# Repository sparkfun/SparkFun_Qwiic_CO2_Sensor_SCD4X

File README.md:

SparkFun CO₂ Humidity and Temperature Sensor - SCD4x (Qwiic)
========================================

<table class="table table-hover table-striped table-bordered">
    <tr>
        <th class="text-center">
        </th>
        <th class="text-center">
        </th>
    </tr>
    <tr align="center">
        <td></td>
        <td></td>
    </tr>
    <tr align="center">
        <td><a href="https://www.sparkfun.com/products/22395">SparkFun CO₂ Humidity and Temperature Sensor - SCD40 (Qwiic)</a></td>
        <td><a href="https://www.sparkfun.com/products/22396">SparkFun CO₂ Humidity and Temperature Sensor - SCD41 (Qwiic)</a></td>
    </tr>
</table>

The SparkFun CO<sub>2</sub> Humidity and Temperature Sensor - SCD4x (Qwiic) features the SCD40 and SCD41 CO<sub>2</sub> sensors from Sensirion<sup>&copy;</sup>. The SCD4x sensors use Sensirion's PASens<sup>&reg;</sup> photoacoustic measurement system that combines narrow-band IR light and a microphone inside the sensing package capable of detecting concentrations from 0 to 40000 ppm with high accuracy. The SCD40 has best accuracy over 400-2000 ppm ±(50 ppm+5%) and the SCD41 has best accuracy over 400-5000 ppm ±(40 ppm+5%). The SCD4x have an integrated temperature and humidity CMos<sup>&reg;</sup> sensor to improve accuracy. For additional accuracy the SCD4x also accept ambient pressure readings!

Repository Contents
-------------------

* **/Documentation** - Data sheets, additional product information
* **/Hardware** - Eagle design files (.brd, .sch)
* **/Production** - Production panel files (.brd)
* **/docs** - Online documentation files

Documentation
--------------
* **[SparkFun SCD4x CO<sub>2</sub> Sensor Arduino Library](https://github.com/sparkfun/SparkFun_SCD4x_Arduino_Library)** - Arduino library for the SparkFun CO₂ Humidity and Temperature Sensor - SCD4x (Qwiic).
* **[Hookup Guide](https://sparkfun.github.io/SparkFun_Qwiic_CO2_Sensor_SCD4X)** - Basic hookup guide for the SparkFun Qwiic CO<sub>2</sub> Sensor - SCD4x.
* **[SparkFun Fritzing repo](https://github.com/sparkfun/Fritzing_Parts)** - Fritzing diagrams for SparkFun products.

Product Versions
----------------
* [SEN-22935](https://www.sparkfun.com/products/22395) - Qwiic CO<sub>2</sub> Sensor - SCD40
* [SEN-22396](https://www.sparkfun.com/products/22395) - Qwiic CO<sub>2</sub> Sensor - SCD41

Version History
---------------
* [SCD40 v10](https://www.sparkfun.com/products/22395) - Initial SparkFun release (SCD40)
* [SCD41 v10](https://www.sparkfun.com/products/22396) - Initial SparkFun release (SCD41)
* [SparkX SCD40 v01](https://www.sparkfun.com/products/18365) - Initial SparkX release (SCD40)
* [SparkX SCD41 v01](https://www.sparkfun.com/products/18366) - Initial SparkX release (SCD41)

License Information
-------------------

This product is _**open source**_!

Please review the LICENSE.md file for license information.

If you have any questions or concerns on licensing, please contact technical support on our [SparkFun forums](https://forum.sparkfun.com/viewforum.php?f=152).

Distributed as-is; no warranty is given.

- Your friends at SparkFun.

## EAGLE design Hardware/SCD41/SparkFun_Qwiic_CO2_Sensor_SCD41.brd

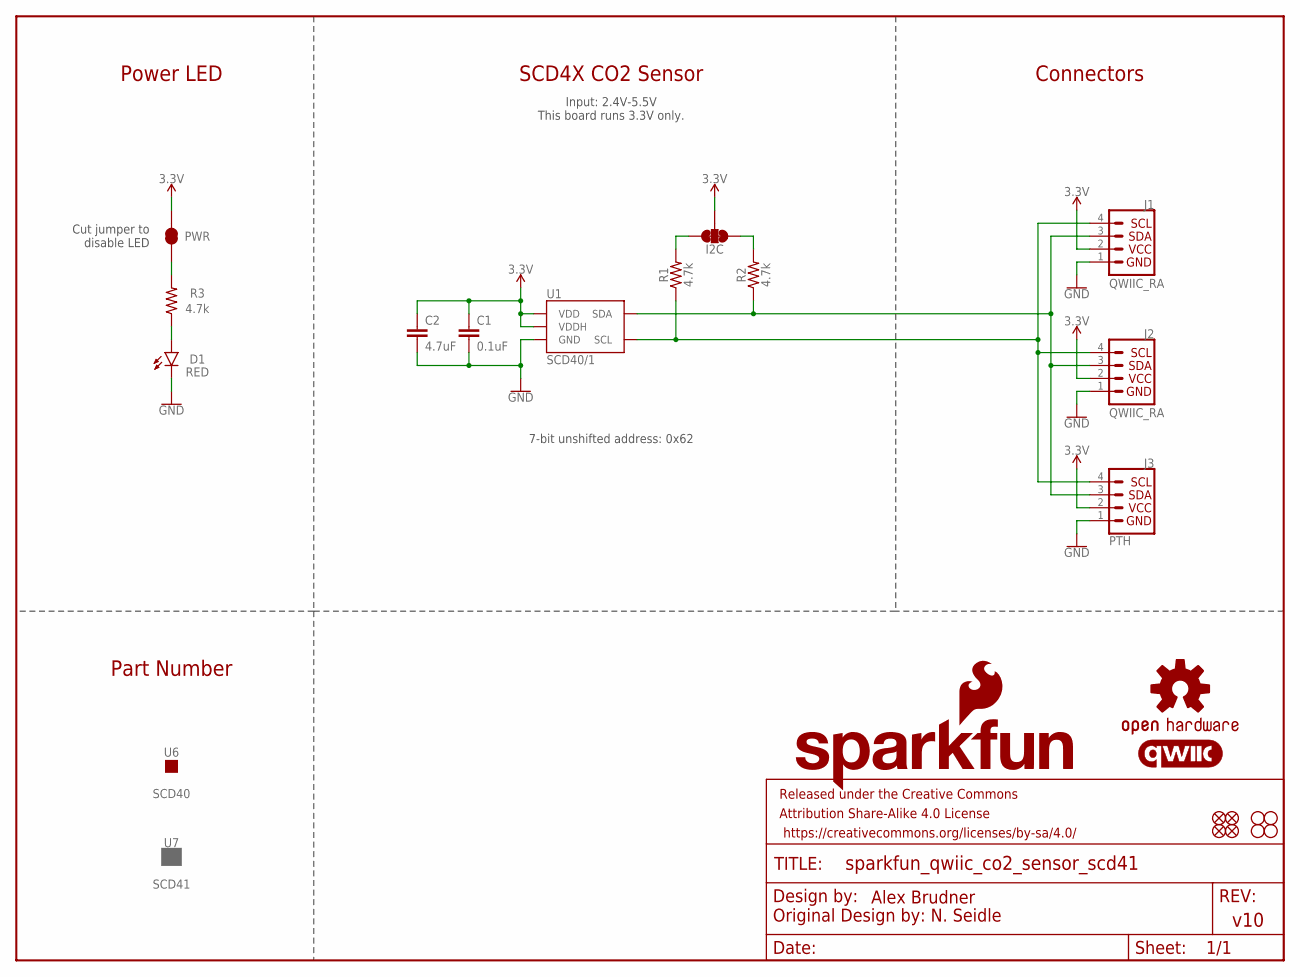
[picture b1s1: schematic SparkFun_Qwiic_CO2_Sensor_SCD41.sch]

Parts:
C1: 0.1uF; 0603
C2: 4.7uF; 0603
D1: RED; LED-0603
FD1, FD2, FD3, FD4: FIDUCIALUFIDUCIAL; FIDUCIAL-MICRO
FRAME1: FRAME-LETTER; CREATIVE_COMMONS
H1, H2, H3, H4: STAND-OFF
I2C: I2C; SMT-JUMPER_3_2-NC_TRACE_SILK
J1, J2: QWIIC_RA; JST04_1MM_RA
J3: PTH; 1X04_NO_SILK
LOGO1: QWIIC_LOGO_CONNECTOR; QWIIC_5.5MM
LOGO2: OSHW-LOGOS; OSHW-LOGO-S
LOGO3: SFE_LOGO_NAME_FLAMEBLANK; BLANK
PWR: PWR; SMT-JUMPER_2_NC_TRACE_SILK
R1, R2, R3: 4.7k; 0603
U1: SCD40/1; SCD4X
U6: SCD40; PRODUCT_IDENT_NO_NO-SILK
U7: SCD41; PRODUCT_IDENT_PASTE_NO-SILK

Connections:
3.3V: C1.1, C2.1, I2C.2, J1.2, J2.2, J3.2, PWR.2, U1.7 (VDD), U1.19 (VDDH)
GND: C1.2, C2.2, D1.C, J1.1, J2.1, J3.1, U1.6 (GND), U1.20 (GND), U1.CP (GND)
unnamed: I2C.1, R2.2
unnamed: I2C.3, R1.2
unnamed: PWR.1, R3.2
unnamed: D1.A, R3.1
SCL: J1.4, J2.4, J3.4, R1.1, U1.9 (SCL)
SDA: J1.3, J2.3, J3.3, R2.1, U1.10 (SDA)

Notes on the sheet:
Cut jumper to disable LED
SCD4X CO2 Sensor
Power LED
Connectors
Part Number
Input: 2.4V-5.5V This board runs 3.3V only.
7-bit unshifted address: 0x62

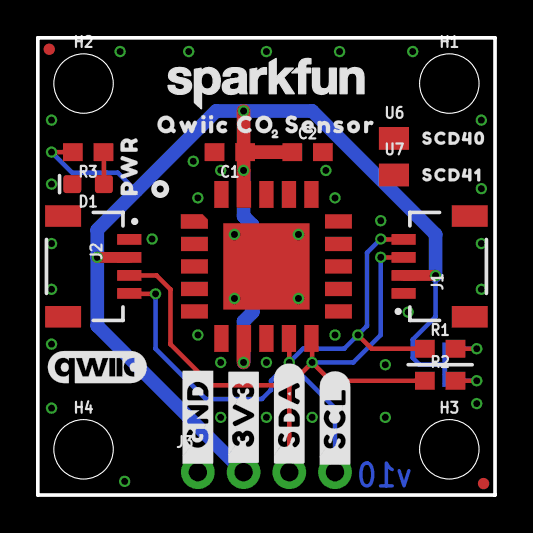
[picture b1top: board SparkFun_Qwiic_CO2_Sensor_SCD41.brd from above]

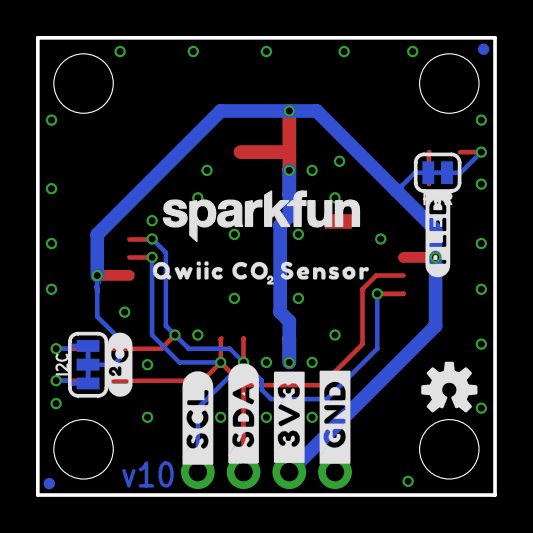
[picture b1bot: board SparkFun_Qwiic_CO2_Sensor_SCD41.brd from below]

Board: 2 copper layers, 25.4 x 25.4 mm, 49 parts (16 on the bottom side), 8 nets.

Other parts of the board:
U$1, U$18: #_GND#14
U$2, U$19: #_3V3#15
U$3, U$20: #_SDA#15
U$4, U$21: #_SCL#16
U$5, U$12: SFE_LOGO_NAME_.1
U$6: SCD414140404021
U$7: SCD40414140404022
U$8, U$13: QWIIC_CO0
U$9, U$14: SENSOR0
U$10, U$15: 20
U$11: SFE_LOGO_FLAME_STOP_.1
U$16: #PLED#21
U$17: #I�C#0
U$22: ORDERING_INSTRUCTIONS
U$23: PWR0

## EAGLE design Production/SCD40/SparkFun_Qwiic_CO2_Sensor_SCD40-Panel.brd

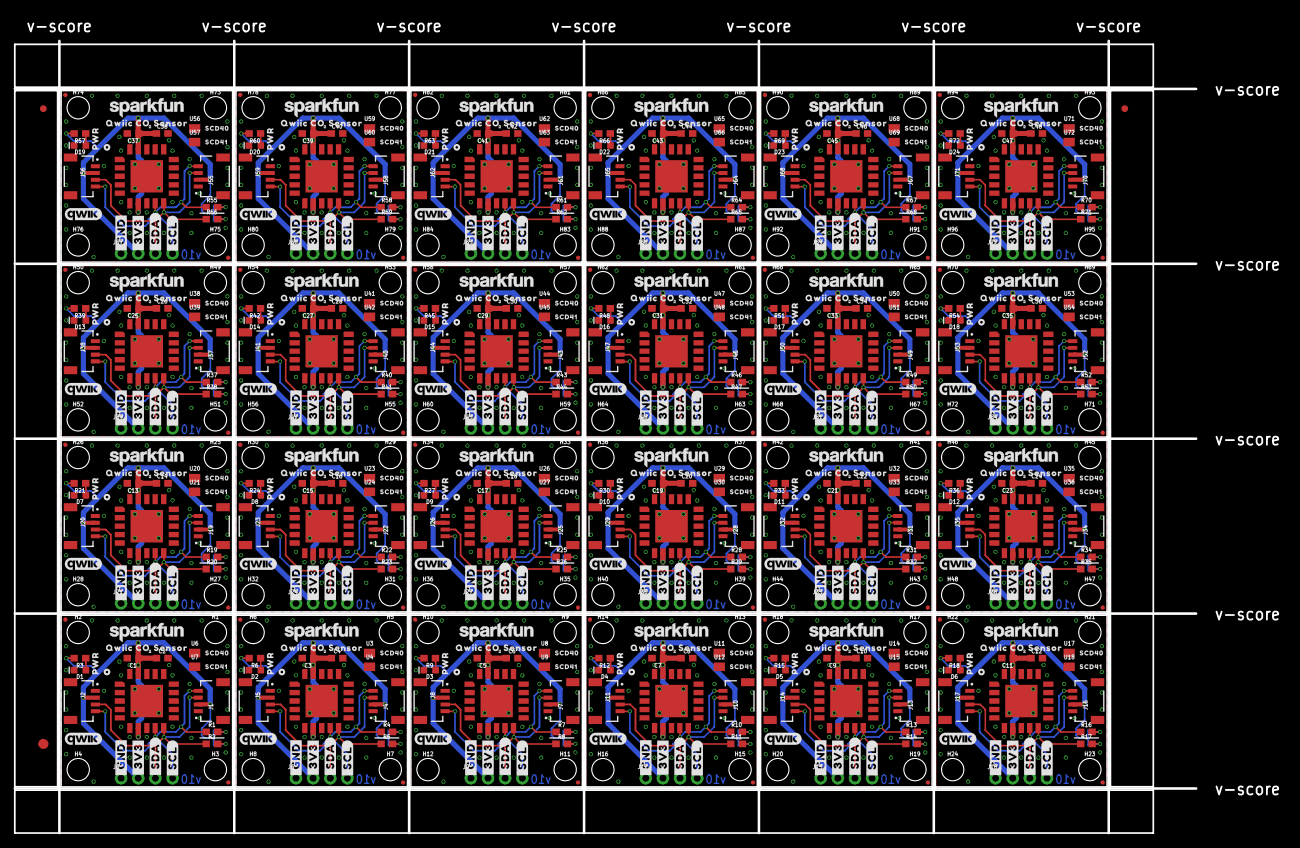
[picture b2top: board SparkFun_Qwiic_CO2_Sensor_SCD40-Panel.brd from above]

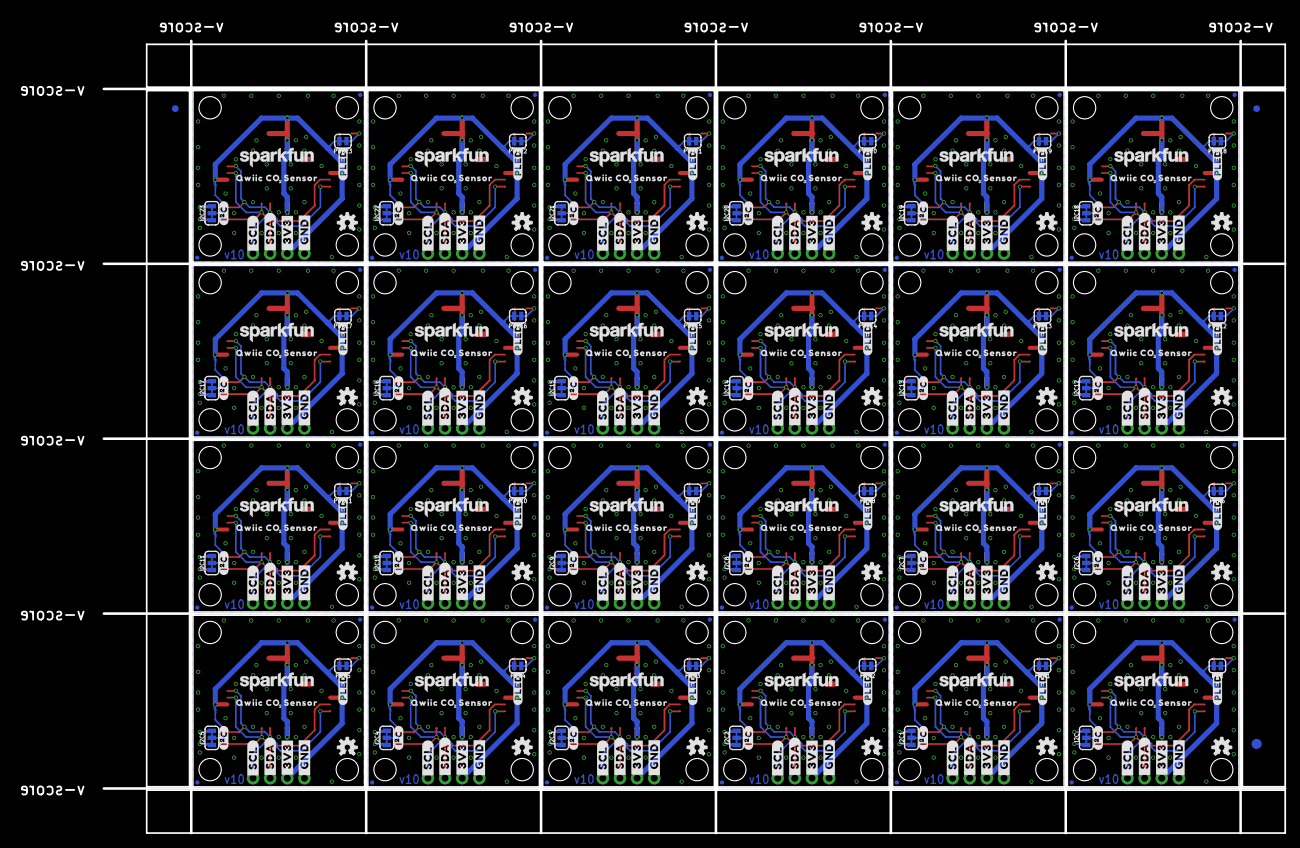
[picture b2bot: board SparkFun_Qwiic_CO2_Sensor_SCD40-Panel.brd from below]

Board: 2 copper layers, 175.0 x 117.3 mm, 1134 parts (387 on the bottom side), 192 nets.

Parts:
C1, C3, C5, C7, C9, C11, C13, C15, C17, C19, C21, C23, C25, C27, C29, C31, C33, C35, C37, C39, C41, C43, C45, C47: 0.1uF; 0603
C2, C4, C6, C8, C10, C12, C14, C16, C18, C20, C22, C24, C26, C28, C30, C32, C34, C36, C38, C40, C42, C44, C46, C48: 4.7uF; 0603
D1, D2, D3, D4, D5, D6, D7, D8, D9, D10, D11, D12, D13, D14, D15, D16, D17, D18, D19, D20, D21, D22, D23, D24: RED; LED-0603
E$1, E$2, E$3, E$4: FIDUCIAL-1X2
E$5, E$6: FIDUCIAL-1.5X3
FD1, FD2, FD3, FD4, FD5, FD6, FD7, FD8, FD9, FD10, FD11, FD12, FD13, FD14, FD15, FD16, FD17, FD18, FD19, FD20, FD21, FD22, FD23, FD24, FD25, FD26, FD27, FD28, FD29, FD30, FD31, FD32, FD33, FD34, FD35, FD36, FD37, FD38, FD39, FD40, FD41, FD42, FD43, FD44, FD45, FD46, FD47, FD48, FD49, FD50, FD51, FD52, FD53, FD54, FD55, FD56, FD57, FD58, FD59, FD60, FD61, FD62, FD63, FD64, FD65, FD66, FD67, FD68, FD69, FD70, FD71, FD72, FD73, FD74, FD75, FD76, FD77, FD78, FD79, FD80, FD81, FD82, FD83, FD84, FD85, FD86, FD87, FD88, FD89, FD90, FD91, FD92, FD93, FD94, FD95, FD96: FIDUCIALUFIDUCIAL; FIDUCIAL-MICRO
H1, H2, H3, H4, H5, H6, H7, H8, H9, H10, H11, H12, H13, H14, H15, H16, H17, H18, H19, H20, H21, H22, H23, H24, H25, H26, H27, H28, H29, H30, H31, H32, H33, H34, H35, H36, H37, H38, H39, H40, H41, H42, H43, H44, H45, H46, H47, H48, H49, H50, H51, H52, H53, H54, H55, H56, H57, H58, H59, H60, H61, H62, H63, H64, H65, H66, H67, H68, H69, H70, H71, H72, H73, H74, H75, H76, H77, H78, H79, H80, H81, H82, H83, H84, H85, H86, H87, H88, H89, H90, H91, H92, H93, H94, H95, H96: STAND-OFF
I2C, I2C1, I2C2, I2C3, I2C4, I2C5, I2C6, I2C7, I2C8, I2C9, I2C10, I2C11, I2C12, I2C13, I2C14, I2C15, I2C16, I2C17, I2C18, I2C19, I2C20, I2C21, I2C22, I2C23: I2C; SMT-JUMPER_3_2-NC_TRACE_SILK
J1, J2, J4, J5, J7, J8, J10, J11, J13, J14, J16, J17, J19, J20, J22, J23, J25, J26, J28, J29, J31, J32, J34, J35, J37, J38, J40, J41, J43, J44, J46, J47, J49, J50, J52, J53, J55, J56, J58, J59, J61, J62, J64, J65, J67, J68, J70, J71: QWIIC_RA; JST04_1MM_RA
J3, J6, J9, J12, J15, J18, J21, J24, J27, J30, J33, J36, J39, J42, J45, J48, J51, J54, J57, J60, J63, J66, J69, J72: PTH; 1X04_NO_SILK
LOGO1, LOGO4, LOGO7, LOGO10, LOGO13, LOGO16, LOGO19, LOGO22, LOGO25, LOGO28, LOGO31, LOGO34, LOGO37, LOGO40, LOGO43, LOGO46, LOGO49, LOGO52, LOGO55, LOGO58, LOGO61, LOGO64, LOGO67, LOGO70: QWIIC_LOGO_CONNECTOR; QWIIC_5.5MM
LOGO2, LOGO5, LOGO8, LOGO11, LOGO14, LOGO17, LOGO20, LOGO23, LOGO26, LOGO29, LOGO32, LOGO35, LOGO38, LOGO41, LOGO44, LOGO47, LOGO50, LOGO53, LOGO56, LOGO59, LOGO62, LOGO65, LOGO68, LOGO71: OSHW-LOGOS; OSHW-LOGO-S
LOGO3, LOGO6, LOGO9, LOGO12, LOGO15, LOGO18, LOGO21, LOGO24, LOGO27, LOGO30, LOGO33, LOGO36, LOGO39, LOGO42, LOGO45, LOGO48, LOGO51, LOGO54, LOGO57, LOGO60, LOGO63, LOGO66, LOGO69, LOGO72: SFE_LOGO_NAME_FLAMEBLANK; BLANK
PWR, PWR1, PWR2, PWR3, PWR4, PWR5, PWR6, PWR7, PWR8, PWR9, PWR10, PWR11, PWR12, PWR13, PWR14, PWR15, PWR16, PWR17, PWR18, PWR19, PWR20, PWR21, PWR22, PWR23: PWR; SMT-JUMPER_2_NC_TRACE_SILK
R1, R2, R4, R5, R7, R8, R10, R11, R13, R14, R16, R17, R19, R20, R22, R23, R25, R26, R28, R29, R31, R32, R34, R35, R37, R38, R40, R41, R43, R44, R46, R47, R49, R50, R52, R53, R55, R56, R58, R59, R61, R62, R64, R65, R67, R68, R70, R71: 2.2k; 0603
R3, R6, R9, R12, R15, R18, R21, R24, R27, R30, R33, R36, R39, R42, R45, R48, R51, R54, R57, R60, R63, R66, R69, R72: 4.7k; 0603
U1, U2, U5, U10, U13, U16, U19, U22, U25, U28, U31, U34, U37, U40, U43, U46, U49, U52, U55, U58, U61, U64, U67, U70: SCD40/1; SCD4X
U3, U6, U8, U11, U14, U17, U20, U23, U26, U29, U32, U35, U38, U41, U44, U47, U50, U53, U56, U59, U62, U65, U68, U71: SCD40; PRODUCT_IDENT_PASTE_NO-SILK
U4, U7, U9, U12, U15, U18, U21, U24, U27, U30, U33, U36, U39, U42, U45, U48, U51, U54, U57, U60, U63, U66, U69, U72: SCD41; PRODUCT_IDENT_NO_NO-SILK
U$1, U$18, U$22, U$39, U$45, U$61, U$67, U$83, U$89, U$105, U$111, U$127, U$133, U$149, U$155, U$171, U$177, U$193, U$199, U$215, U$221, U$237, U$243, U$259, U$265, U$281, U$287, U$303, U$309, U$325, U$331, U$347, U$353, U$369, U$375, U$391, U$397, U$413, U$419, U$435, U$441, U$457, U$463, U$479, U$485, U$501, U$507, U$523: #_GND#14
U$2, U$19, U$24, U$40, U$46, U$62, U$68, U$84, U$90, U$106, U$112, U$128, U$134, U$150, U$156, U$172, U$178, U$194, U$200, U$216, U$222, U$238, U$244, U$260, U$266, U$282, U$288, U$304, U$310, U$326, U$332, U$348, U$354, U$370, U$376, U$392, U$398, U$414, U$420, U$436, U$442, U$458, U$464, U$480, U$486, U$502, U$508, U$524: #_3V3#15
U$3, U$20, U$25, U$41, U$47, U$63, U$69, U$85, U$91, U$107, U$113, U$129, U$135, U$151, U$157, U$173, U$179, U$195, U$201, U$217, U$223, U$239, U$245, U$261, U$267, U$283, U$289, U$305, U$311, U$327, U$333, U$349, U$355, U$371, U$377, U$393, U$399, U$415, U$421, U$437, U$443, U$459, U$465, U$481, U$487, U$503, U$509, U$525: #_SDA#15
U$4, U$21, U$26, U$42, U$48, U$64, U$70, U$86, U$92, U$108, U$114, U$130, U$136, U$152, U$158, U$174, U$180, U$196, U$202, U$218, U$224, U$240, U$246, U$262, U$268, U$284, U$290, U$306, U$312, U$328, U$334, U$350, U$356, U$372, U$378, U$394, U$400, U$416, U$422, U$438, U$444, U$460, U$466, U$482, U$488, U$504, U$510, U$526: #_SCL#16
U$5, U$12, U$27, U$34, U$49, U$56, U$71, U$78, U$93, U$100, U$115, U$122, U$137, U$144, U$159, U$166, U$181, U$188, U$203, U$210, U$225, U$232, U$247, U$254, U$269, U$276, U$291, U$298, U$313, U$320, U$335, U$342, U$357, U$364, U$379, U$386, U$401, U$408, U$423, U$430, U$445, U$452, U$467, U$474, U$489, U$496, U$511, U$518: SFE_LOGO_NAME_.1
U$6, U$28, U$50, U$72, U$94, U$116, U$138, U$160, U$182, U$204, U$226, U$248, U$270, U$292, U$314, U$336, U$358, U$380, U$402, U$424, U$446, U$468, U$490, U$512: SCD414140404021
U$7, U$29, U$51, U$73, U$95, U$117, U$139, U$161, U$183, U$205, U$227, U$249, U$271, U$293, U$315, U$337, U$359, U$381, U$403, U$425, U$447, U$469, U$491, U$513: SCD40414140404022
U$8, U$13, U$30, U$35, U$52, U$57, U$74, U$79, U$96, U$101, U$118, U$123, U$140, U$145, U$162, U$167, U$184, U$189, U$206, U$211, U$228, U$233, U$250, U$255, U$272, U$277, U$294, U$299, U$316, U$321, U$338, U$343, U$360, U$365, U$382, U$387, U$404, U$409, U$426, U$431, U$448, U$453, U$470, U$475, U$492, U$497, U$514, U$519: QWIIC_CO0
U$9, U$14, U$31, U$36, U$53, U$58, U$75, U$80, U$97, U$102, U$119, U$124, U$141, U$146, U$163, U$168, U$185, U$190, U$207, U$212, U$229, U$234, U$251, U$256, U$273, U$278, U$295, U$300, U$317, U$322, U$339, U$344, U$361, U$366, U$383, U$388, U$405, U$410, U$427, U$432, U$449, U$454, U$471, U$476, U$493, U$498, U$515, U$520: SENSOR0
U$10, U$15, U$32, U$37, U$54, U$59, U$76, U$81, U$98, U$103, U$120, U$125, U$142, U$147, U$164, U$169, U$186, U$191, U$208, U$213, U$230, U$235, U$252, U$257, U$274, U$279, U$296, U$301, U$318, U$323, U$340, U$345, U$362, U$367, U$384, U$389, U$406, U$411, U$428, U$433, U$450, U$455, U$472, U$477, U$494, U$499, U$516, U$521: 20
U$11, U$33, U$55, U$77, U$99, U$121, U$143, U$165, U$187, U$209, U$231, U$253, U$275, U$297, U$319, U$341, U$363, U$385, U$407, U$429, U$451, U$473, U$495, U$517: SFE_LOGO_FLAME_STOP_.1
U$16, U$38, U$60, U$82, U$104, U$126, U$148, U$170, U$192, U$214, U$236, U$258, U$280, U$302, U$324, U$346, U$368, U$390, U$412, U$434, U$456, U$478, U$500, U$522: #PLED#21
U$17, U$43, U$65, U$87, U$109, U$131, U$153, U$175, U$197, U$219, U$241, U$263, U$285, U$307, U$329, U$351, U$373, U$395, U$417, U$439, U$461, U$483, U$505, U$527: #I�C#0
U$23, U$44, U$66, U$88, U$110, U$132, U$154, U$176, U$198, U$220, U$242, U$264, U$286, U$308, U$330, U$352, U$374, U$396, U$418, U$440, U$462, U$484, U$506, U$528: PWR0

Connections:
3.3V: C1.1, C2.1, I2C.2, J1.2, J2.2, J3.2, PWR.2, U1.7, U1.19
3.3V1: C3.1, C4.1, I2C1.2, J4.2, J5.2, J6.2, PWR1.2, U2.7, U2.19
3.3V2: C5.1, C6.1, I2C2.2, J7.2, J8.2, J9.2, PWR2.2, U5.7, U5.19
3.3V3: C7.1, C8.1, I2C3.2, J10.2, J11.2, J12.2, PWR3.2, U10.7, U10.19
3.3V4: C9.1, C10.1, I2C4.2, J13.2, J14.2, J15.2, PWR4.2, U13.7, U13.19
3.3V5: C11.1, C12.1, I2C5.2, J16.2, J17.2, J18.2, PWR5.2, U16.7, U16.19
3.3V6: C13.1, C14.1, I2C6.2, J19.2, J20.2, J21.2, PWR6.2, U19.7, U19.19
3.3V7: C15.1, C16.1, I2C7.2, J22.2, J23.2, J24.2, PWR7.2, U22.7, U22.19
3.3V8: C17.1, C18.1, I2C8.2, J25.2, J26.2, J27.2, PWR8.2, U25.7, U25.19
3.3V9: C19.1, C20.1, I2C9.2, J28.2, J29.2, J30.2, PWR9.2, U28.7, U28.19
3.3V10: C21.1, C22.1, I2C10.2, J31.2, J32.2, J33.2, PWR10.2, U31.7, U31.19
3.3V11: C23.1, C24.1, I2C11.2, J34.2, J35.2, J36.2, PWR11.2, U34.7, U34.19
3.3V12: C25.1, C26.1, I2C12.2, J37.2, J38.2, J39.2, PWR12.2, U37.7, U37.19
3.3V13: C27.1, C28.1, I2C13.2, J40.2, J41.2, J42.2, PWR13.2, U40.7, U40.19
3.3V14: C29.1, C30.1, I2C14.2, J43.2, J44.2, J45.2, PWR14.2, U43.7, U43.19
3.3V15: C31.1, C32.1, I2C15.2, J46.2, J47.2, J48.2, PWR15.2, U46.7, U46.19
3.3V16: C33.1, C34.1, I2C16.2, J49.2, J50.2, J51.2, PWR16.2, U49.7, U49.19
3.3V17: C35.1, C36.1, I2C17.2, J52.2, J53.2, J54.2, PWR17.2, U52.7, U52.19
3.3V18: C37.1, C38.1, I2C18.2, J55.2, J56.2, J57.2, PWR18.2, U55.7, U55.19
3.3V19: C39.1, C40.1, I2C19.2, J58.2, J59.2, J60.2, PWR19.2, U58.7, U58.19
3.3V20: C41.1, C42.1, I2C20.2, J61.2, J62.2, J63.2, PWR20.2, U61.7, U61.19
3.3V21: C43.1, C44.1, I2C21.2, J64.2, J65.2, J66.2, PWR21.2, U64.7, U64.19
3.3V22: C45.1, C46.1, I2C22.2, J67.2, J68.2, J69.2, PWR22.2, U67.7, U67.19
3.3V23: C47.1, C48.1, I2C23.2, J70.2, J71.2, J72.2, PWR23.2, U70.7, U70.19
GND: C1.2, C2.2, D1.C, J1.1, J2.1, J3.1, U1.6, U1.20, U1.CP
GND1: C3.2, C4.2, D2.C, J4.1, J5.1, J6.1, U2.6, U2.20, U2.CP
GND2: C5.2, C6.2, D3.C, J7.1, J8.1, J9.1, U5.6, U5.20, U5.CP
GND3: C7.2, C8.2, D4.C, J10.1, J11.1, J12.1, U10.6, U10.20, U10.CP
GND4: C9.2, C10.2, D5.C, J13.1, J14.1, J15.1, U13.6, U13.20, U13.CP
GND5: C11.2, C12.2, D6.C, J16.1, J17.1, J18.1, U16.6, U16.20, U16.CP
GND6: C13.2, C14.2, D7.C, J19.1, J20.1, J21.1, U19.6, U19.20, U19.CP
GND7: C15.2, C16.2, D8.C, J22.1, J23.1, J24.1, U22.6, U22.20, U22.CP
GND8: C17.2, C18.2, D9.C, J25.1, J26.1, J27.1, U25.6, U25.20, U25.CP
GND9: C19.2, C20.2, D10.C, J28.1, J29.1, J30.1, U28.6, U28.20, U28.CP
GND10: C21.2, C22.2, D11.C, J31.1, J32.1, J33.1, U31.6, U31.20, U31.CP
GND11: C23.2, C24.2, D12.C, J34.1, J35.1, J36.1, U34.6, U34.20, U34.CP
GND12: C25.2, C26.2, D13.C, J37.1, J38.1, J39.1, U37.6, U37.20, U37.CP
GND13: C27.2, C28.2, D14.C, J40.1, J41.1, J42.1, U40.6, U40.20, U40.CP
GND14: C29.2, C30.2, D15.C, J43.1, J44.1, J45.1, U43.6, U43.20, U43.CP
GND15: C31.2, C32.2, D16.C, J46.1, J47.1, J48.1, U46.6, U46.20, U46.CP
GND16: C33.2, C34.2, D17.C, J49.1, J50.1, J51.1, U49.6, U49.20, U49.CP
GND17: C35.2, C36.2, D18.C, J52.1, J53.1, J54.1, U52.6, U52.20, U52.CP
GND18: C37.2, C38.2, D19.C, J55.1, J56.1, J57.1, U55.6, U55.20, U55.CP
GND19: C39.2, C40.2, D20.C, J58.1, J59.1, J60.1, U58.6, U58.20, U58.CP
GND20: C41.2, C42.2, D21.C, J61.1, J62.1, J63.1, U61.6, U61.20, U61.CP
GND21: C43.2, C44.2, D22.C, J64.1, J65.1, J66.1, U64.6, U64.20, U64.CP
GND22: C45.2, C46.2, D23.C, J67.1, J68.1, J69.1, U67.6, U67.20, U67.CP
GND23: C47.2, C48.2, D24.C, J70.1, J71.1, J72.1, U70.6, U70.20, U70.CP
unnamed: I2C1.1, R5.2
unnamed: I2C1.3, R4.2
unnamed: I2C.1, R2.2
unnamed: I2C.3, R1.2
unnamed: PWR.1, R3.2
unnamed: D1.A, R3.1
unnamed: PWR1.1, R6.2
unnamed: D2.A, R6.1
unnamed: I2C2.1, R8.2
unnamed: I2C2.3, R7.2
unnamed: PWR2.1, R9.2
unnamed: D3.A, R9.1
unnamed: I2C3.1, R11.2
unnamed: I2C3.3, R10.2
unnamed: PWR3.1, R12.2
unnamed: D4.A, R12.1
unnamed: I2C4.1, R14.2
unnamed: I2C4.3, R13.2
unnamed: PWR4.1, R15.2
unnamed: D5.A, R15.1
unnamed: I2C5.1, R17.2
unnamed: I2C5.3, R16.2
unnamed: PWR5.1, R18.2
unnamed: D6.A, R18.1
unnamed: I2C6.1, R20.2
unnamed: I2C6.3, R19.2
unnamed: PWR6.1, R21.2
unnamed: D7.A, R21.1
unnamed: I2C7.1, R23.2
unnamed: I2C7.3, R22.2
unnamed: PWR7.1, R24.2
unnamed: D8.A, R24.1
unnamed: I2C8.1, R26.2
unnamed: I2C8.3, R25.2
unnamed: PWR8.1, R27.2
unnamed: D9.A, R27.1
unnamed: I2C9.1, R29.2
unnamed: I2C9.3, R28.2
unnamed: PWR9.1, R30.2
unnamed: D10.A, R30.1
unnamed: I2C10.1, R32.2
unnamed: I2C10.3, R31.2
unnamed: PWR10.1, R33.2
unnamed: D11.A, R33.1
unnamed: I2C11.1, R35.2
unnamed: I2C11.3, R34.2
unnamed: PWR11.1, R36.2
unnamed: D12.A, R36.1
unnamed: I2C12.1, R38.2
unnamed: I2C12.3, R37.2
unnamed: PWR12.1, R39.2
unnamed: D13.A, R39.1
unnamed: I2C13.1, R41.2
unnamed: I2C13.3, R40.2
unnamed: PWR13.1, R42.2
unnamed: D14.A, R42.1
unnamed: I2C14.1, R44.2
unnamed: I2C14.3, R43.2
unnamed: PWR14.1, R45.2
unnamed: D15.A, R45.1
unnamed: I2C15.1, R47.2
unnamed: I2C15.3, R46.2
unnamed: PWR15.1, R48.2
unnamed: D16.A, R48.1
unnamed: I2C16.1, R50.2
unnamed: I2C16.3, R49.2
unnamed: PWR16.1, R51.2
unnamed: D17.A, R51.1
unnamed: I2C17.1, R53.2
unnamed: I2C17.3, R52.2
unnamed: PWR17.1, R54.2
unnamed: D18.A, R54.1
unnamed: I2C18.1, R56.2
unnamed: I2C18.3, R55.2
unnamed: PWR18.1, R57.2
unnamed: D19.A, R57.1
unnamed: I2C19.1, R59.2
unnamed: I2C19.3, R58.2
unnamed: PWR19.1, R60.2
unnamed: D20.A, R60.1
unnamed: I2C20.1, R62.2
unnamed: I2C20.3, R61.2
unnamed: PWR20.1, R63.2
unnamed: D21.A, R63.1
unnamed: I2C21.1, R65.2
unnamed: I2C21.3, R64.2
unnamed: PWR21.1, R66.2
unnamed: D22.A, R66.1
unnamed: I2C22.1, R68.2
unnamed: I2C22.3, R67.2
unnamed: PWR22.1, R69.2
unnamed: D23.A, R69.1
unnamed: I2C23.1, R71.2
unnamed: I2C23.3, R70.2
unnamed: PWR23.1, R72.2
unnamed: D24.A, R72.1
SCL: J1.4, J2.4, J3.4, R1.1, U1.9
SCL1: J4.4, J5.4, J6.4, R4.1, U2.9
SCL2: J7.4, J8.4, J9.4, R7.1, U5.9
SCL3: J10.4, J11.4, J12.4, R10.1, U10.9
SCL4: J13.4, J14.4, J15.4, R13.1, U13.9
SCL5: J16.4, J17.4, J18.4, R16.1, U16.9
SCL6: J19.4, J20.4, J21.4, R19.1, U19.9
SCL7: J22.4, J23.4, J24.4, R22.1, U22.9
SCL8: J25.4, J26.4, J27.4, R25.1, U25.9
SCL9: J28.4, J29.4, J30.4, R28.1, U28.9
SCL10: J31.4, J32.4, J33.4, R31.1, U31.9
SCL11: J34.4, J35.4, J36.4, R34.1, U34.9
SCL12: J37.4, J38.4, J39.4, R37.1, U37.9
SCL13: J40.4, J41.4, J42.4, R40.1, U40.9
SCL14: J43.4, J44.4, J45.4, R43.1, U43.9
SCL15: J46.4, J47.4, J48.4, R46.1, U46.9
SCL16: J49.4, J50.4, J51.4, R49.1, U49.9
SCL17: J52.4, J53.4, J54.4, R52.1, U52.9
SCL18: J55.4, J56.4, J57.4, R55.1, U55.9
SCL19: J58.4, J59.4, J60.4, R58.1, U58.9
SCL20: J61.4, J62.4, J63.4, R61.1, U61.9
SCL21: J64.4, J65.4, J66.4, R64.1, U64.9
SCL22: J67.4, J68.4, J69.4, R67.1, U67.9
SCL23: J70.4, J71.4, J72.4, R70.1, U70.9
SDA: J1.3, J2.3, J3.3, R2.1, U1.10
SDA1: J4.3, J5.3, J6.3, R5.1, U2.10
SDA2: J7.3, J8.3, J9.3, R8.1, U5.10
SDA3: J10.3, J11.3, J12.3, R11.1, U10.10
SDA4: J13.3, J14.3, J15.3, R14.1, U13.10
SDA5: J16.3, J17.3, J18.3, R17.1, U16.10
SDA6: J19.3, J20.3, J21.3, R20.1, U19.10
SDA7: J22.3, J23.3, J24.3, R23.1, U22.10
SDA8: J25.3, J26.3, J27.3, R26.1, U25.10
SDA9: J28.3, J29.3, J30.3, R29.1, U28.10
SDA10: J31.3, J32.3, J33.3, R32.1, U31.10
SDA11: J34.3, J35.3, J36.3, R35.1, U34.10
SDA12: J37.3, J38.3, J39.3, R38.1, U37.10
SDA13: J40.3, J41.3, J42.3, R41.1, U40.10
SDA14: J43.3, J44.3, J45.3, R44.1, U43.10
SDA15: J46.3, J47.3, J48.3, R47.1, U46.10
SDA16: J49.3, J50.3, J51.3, R50.1, U49.10
SDA17: J52.3, J53.3, J54.3, R53.1, U52.10
SDA18: J55.3, J56.3, J57.3, R56.1, U55.10
SDA19: J58.3, J59.3, J60.3, R59.1, U58.10
SDA20: J61.3, J62.3, J63.3, R62.1, U61.10
SDA21: J64.3, J65.3, J66.3, R65.1, U64.10
SDA22: J67.3, J68.3, J69.3, R68.1, U67.10
SDA23: J70.3, J71.3, J72.3, R71.1, U70.10

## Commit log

2023-04-26 Remove extra folders.
2023-04-26 Added datasheet.
2023-04-26 Added schematic/board files
    Added panels.
    Added Lib with part.
2023-04-27 Update from pre-design review notes.
    Changed I2C PURs from 4.7k to 2.2k to match Qwiic standards.
    Changed wording on revision.
    Update top stop of pin 1 of sensor.
    Repanelize.
2023-05-11 Initial Docs Commit
    Initial draft of documentation commit. Adding all relevant files for GH pages build.
2023-06-05 Documentation Update
    Update to documentation. Adding photo assets and updating Hookup Guide files. README.md updated from template.
2023-06-06 Update mkdocs.yml
    Moving override to correct location
2023-06-07 Final Review and Image Update
    Final review with minor fixes. Adding Arduino screenshots.
2023-06-07 Publish Actions
    Adding publish actions .yml file and minor updates to page icons.
2023-06-07 Redirect/Header Files
    Adding Index.md redirect and Header.html files.
2023-06-14 Adding Video and minor fixes
    Adding the Product Showcase video to the Intro and fixing Single Page line start errors.
2023-06-15 Update mkdocs.yml
    Fix page build action. Updating branch from docs to main.
2023-06-15 Update mkdocs.yml
    Fix GH pages actions. Updating branch from docs to main
2023-06-15 Deployed 35d9cfb with MkDocs version: 1.4.3
2023-08-02 Update mkdocs.yml
    Adding Google analytics
2023-08-02 Deployed 6549ab8 with MkDocs version: 1.5.2
2024-10-25 Update mkdocs.yml
    Analytics update
2024-10-25 Deployed cc7038a with MkDocs version: 1.6.1

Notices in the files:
parts and their libraries:
SparkFun-Aesthetics: Licensing: Creative Commons ShareAlike 4.0 International - https://creativecommons.org/licenses/by-sa/4.0
SparkFun-Aesthetics: Released under the Creative Commons Attribution Share-Alike 4.0 License
SparkFun-Aesthetics: https://creativecommons.org/licenses/by-sa/4.0
